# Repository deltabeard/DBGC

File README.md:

# DBGC: Deltabeard's Game Boy Cartridge
A reprogrammable Game Boy cartridge that utilises the Raspberry Pi RP2040.

## Supported Features
- Support for No MBC, MBC1 and MBC3 games (but only in single-speed mode).
- Real Time Clock (RTC) with battery backup.
- FRAM 32KiB for save support.
- NOR Flash 16MiB with support upto 8MiB ROM size.
- Can only play the one game programmed in at compile time.
- USB-C firmware upgrade support.

## Proposed Features

- Support multiple games on NOR Flash.
- USB-C flash storage explorer to store and retrieve save files and ROMs.
- USB-C networking support.

### Flash Storage
The flash storage will be partitioned to allow the user to either support large ROM sizes or increased number of ROMs stored. By setting the maximum ROM size to a smaller value, there will be more space to store other ROMs on the *Storage* partition. An example partition scheme is shown below.

| Partition | Size | Purpose |
|-----------|  --: |---------|
| Firmware | 256KiB | Stores firmware for the RP2040 |
| Storage | Remainder | Wear-levelling filesystem holding ROMs and save files |

### USB-C Networking

By utilising RP2040 and TinyUSB features, the USB-C port can act as a networking device, which when attached to a host, will allow the RP2040 to connect to the Internet. Future features will allow supported Game Boy games to make connections to the internet.

## Notes
BOM is optimised for purchase from JLCPCB with SMT assembly. The cost of producing a single cart of this revision is approximately £15. This version of the PCB has major errors that can be seen in the [errata.md](https://github.com/deltabeard/DBGC/blob/master/errata.md) document. **Do not manufacture PCB version 0.3 or below**; instead wait for the next version or the one on the master branch. 

# License

The majority of the software within this project are licensed under the 
terms of the ISC License. Please see the header of each source file for 
license terms. In brief, the copyright and permission notices must not be
modified.

The PCB schematic and layout are licensed under the 
Creative Commons Attribution-ShareAlike 4.0 International (CC BY-SA 4.0) 
license. In brief, you may modify and share but only under the same license 
to allow others to continue modifying and sharing.

This project includes
[Libbet and the Magic Floor](https://github.com/pinobatch/libbet) and
[2048-gb](https://github.com/Sanqui/2048-gb), which are both 
licensed under the terms of the zlib license, and are included within this
project in an unmodified binary form for testing purposes.

# Showcase

- [Pokemon Polished Crystal](https://github.com/Rangi42/polishedcrystal). A 
  major fan-made upgrade to Pokemon Crystal. Uses MBC3 with battery backed 
  SRAM and Real Time Clock. The version tested had CGB double-speed disabled,
  which caused minor graphical glitches within the game. An effort is made to
  fix these graphical glitches at https://github.com/deltabeard/polishedcrystal.
  DBGC does not currently support double-speed, so using it to play
  Polished Crystal may not result in the intended experience.

- Mega Man 1. This commercial game uses MBC1 ROM banking.

- [2048-gb](https://github.com/Sanqui/2048-gb). Open source homebrew game. 
  Uses no ROM banking.

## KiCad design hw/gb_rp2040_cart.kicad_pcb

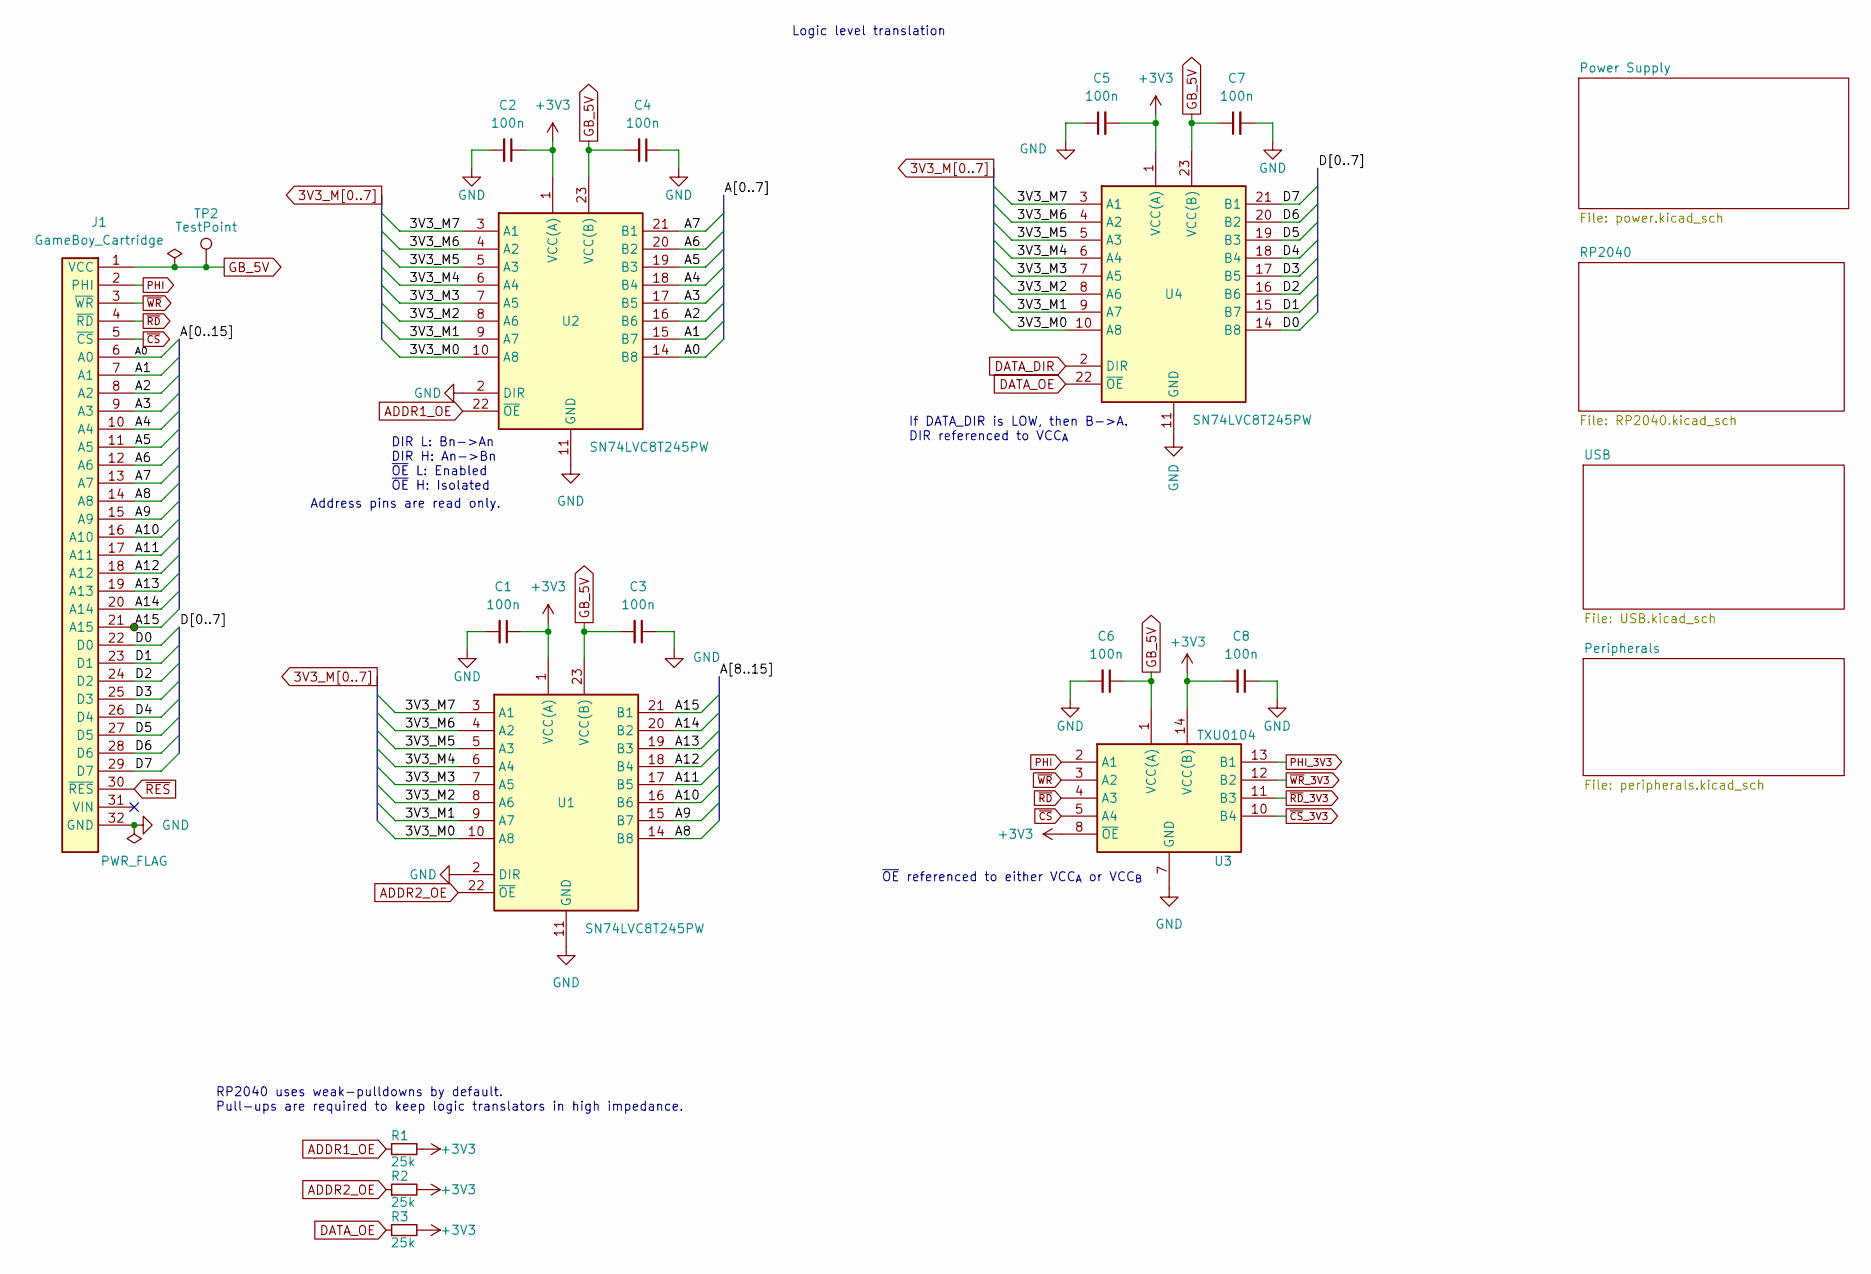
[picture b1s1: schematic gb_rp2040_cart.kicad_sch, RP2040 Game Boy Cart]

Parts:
C1, C2, C3, C4, C5, C6, C7, C8: 100n; C_0402_1005Metric; LCSC C1525
J1: GameBoy_Cartridge; GameBoy_Cartridge_1x32_P1.50mm_Full
R1, R2, R3: 25k; R_0402_1005Metric; LCSC C25900
TP1, TP2: TestPoint; TestPoint_Pad_D1.0mm
U1, U2, U4: SN74LVC8T245PW; TSSOP-24_4.4x7.8mm_P0.65mm; LCSC C27643
U3: TXU0104; TSSOP-14_4.4x5mm_P0.65mm

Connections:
3V3_M0: U1.10 (A8), U2.10 (A8), U4.10 (A8); also elsewhere on the board
3V3_M1: U1.9 (A7), U2.9 (A7), U4.9 (A7); also elsewhere on the board
3V3_M2: U1.8 (A6), U2.8 (A6), U4.8 (A6); also elsewhere on the board
3V3_M3: U1.7 (A5), U2.7 (A5), U4.7 (A5); also elsewhere on the board
3V3_M4: U1.6 (A4), U2.6 (A4), U4.6 (A4); also elsewhere on the board
3V3_M5: U1.5 (A3), U2.5 (A3), U4.5 (A3); also elsewhere on the board
3V3_M6: U1.4 (A2), U2.4 (A2), U4.4 (A2); also elsewhere on the board
3V3_M7: U1.3 (A1), U2.3 (A1), U4.3 (A1); also elsewhere on the board
/A0: J1.6 (A0), U2.14 (B8)
/A1: J1.7 (A1), U2.15 (B7)
/A2: J1.8 (A2), U2.16 (B6)
/A3: J1.9 (A3), U2.17 (B5)
/A4: J1.10 (A4), U2.18 (B4)
/A5: J1.11 (A5), U2.19 (B3)
/A6: J1.12 (A6), U2.20 (B2)
/A7: J1.13 (A7), U2.21 (B1)
/A8: J1.14 (A8), U1.14 (B8)
/A9: J1.15 (A9), U1.15 (B7)
/A10: J1.16 (A10), U1.16 (B6)
/A11: J1.17 (A11), U1.17 (B5)
/A12: J1.18 (A12), U1.18 (B4)
/A13: J1.19 (A13), U1.19 (B3)
/A14: J1.20 (A14), U1.20 (B2)
/A15: J1.21 (A15), TP1.1, U1.21 (B1)
/D0: J1.22 (D0), U4.14 (B8)
/D1: J1.23 (D1), U4.15 (B7)
/D2: J1.24 (D2), U4.16 (B6)
/D3: J1.25 (D3), U4.17 (B5)
/D4: J1.26 (D4), U4.18 (B4)
/D5: J1.27 (D5), U4.19 (B3)
/D6: J1.28 (D6), U4.20 (B2)
/D7: J1.29 (D7), U4.21 (B1)
DATA_DIR: U4.2 (DIR); also elsewhere on the board
DATA_OE: R3.1, U4.22 (~OE); also elsewhere on the board
GB_5V: C3.2, C4.2, C6.1, C7.1, J1.1 (VCC), TP2.1, U1.23 (VCC(B)), U1.24 (VCC(B)), U2.23 (VCC(B)), U2.24 (VCC(B)), U3.1 (VCC(A)), U4.23 (VCC(B)), U4.24 (VCC(B)); also elsewhere on the board
PHI: J1.2 (PHI), U3.2 (A1)
PHI_3V3: U3.13 (B1); also elsewhere on the board
~CS: J1.5 (~CS), U3.5 (A4)
~CS_3V3: U3.10 (B4); also elsewhere on the board
~RD: J1.4 (~RD), U3.4 (A3)
~RD_3V3: U3.11 (B3); also elsewhere on the board
~RES: J1.30 (~RES); also elsewhere on the board
~WR: J1.3 (~WR), U3.3 (A2)
~WR_3V3: U3.12 (B2); also elsewhere on the board

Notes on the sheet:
RP2040 uses weak-pulldowns by default. Pull-ups are required to keep logic translators in high impedance.
Address pins are read only.
DIR L: Bn->An DIR H: An->Bn ~{OE} L: Enabled ~{OE} H: Isolated
Logic level translation
~{OE} referenced to either VCC_{A} or VCC_{B}
If DATA_DIR is LOW, then B->A. DIR referenced to VCC_{A}

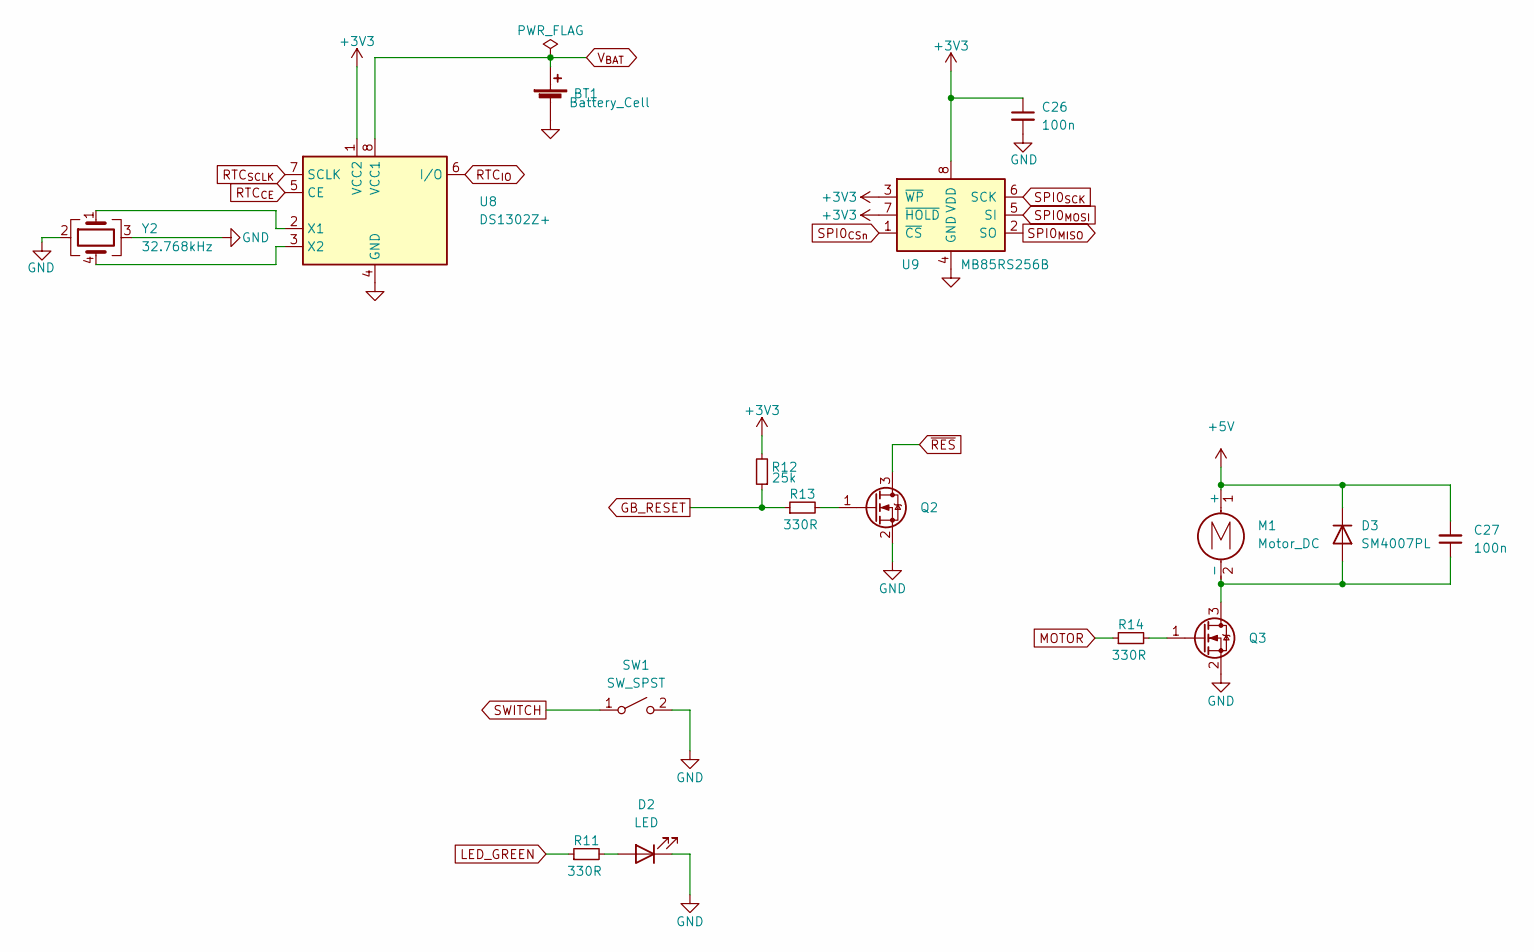
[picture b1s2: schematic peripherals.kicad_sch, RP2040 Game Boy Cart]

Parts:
BT1: Battery_Cell; MY-2032-11; LCSC C964835
C26, C27: 100n; C_0402_1005Metric; LCSC C1525
D2: LED; LED_0603_1608Metric; LCSC C2286
D3: SM4007PL; D_SOD-123F; LCSC C64898
M1: Motor_DC; PinHeader_1x02_P1.27mm_Vertical
Q2, Q3: N-Channel; SOT-23; LCSC C8545
R11, R13, R14: 330R; R_0603_1608Metric; LCSC C23138
R12: 25k; R_0402_1005Metric; LCSC C25900
SW1: SW_SPST; SW_SPST_TL3342; LCSC C318886
U8: DS1302Z+; SOIC-8_3.9x4.9mm_P1.27mm; LCSC C265479
U9: MB85RS256B; SOIC-8_3.9x4.9mm_P1.27mm; LCSC C8742
Y2: 32.768kHz; Crystal_SMD_Abracon_ABS25-4Pin_8.0x3.8mm; LCSC C252402

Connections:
+5V: C27.2, D3.1 (K), M1.1 (+); also elsewhere on the board
GB_RESET: R12.1, R13.1; also elsewhere on the board
LED_GREEN: R11.1; also elsewhere on the board
MOTOR: R14.1; also elsewhere on the board
unnamed: C27.1, D3.2 (A), M1.2 (-), Q3.3 (D)
unnamed: D2.2 (A), R11.2
unnamed: Q2.1 (G), R13.2
unnamed: Q3.1 (G), R14.2
unnamed: U8.2 (X1), Y2.1
unnamed: U8.3 (X2), Y2.4
RTC_{CE}: U8.5 (CE); also elsewhere on the board
RTC_{IO}: U8.6 (I/O); also elsewhere on the board
RTC_{SCLK}: U8.7 (SCLK); also elsewhere on the board
SPI0_{CSn}: U9.1 (~CS); also elsewhere on the board
SPI0_{MISO}: U9.2 (SO); also elsewhere on the board
SPI0_{MOSI}: U9.5 (SI); also elsewhere on the board
SPI0_{SCK}: U9.6 (SCK); also elsewhere on the board
SWITCH: SW1.1 (A); also elsewhere on the board
V_{BAT}: BT1.1 (+), U8.8 (VCC1)
~RES: Q2.3 (D); also elsewhere on the board

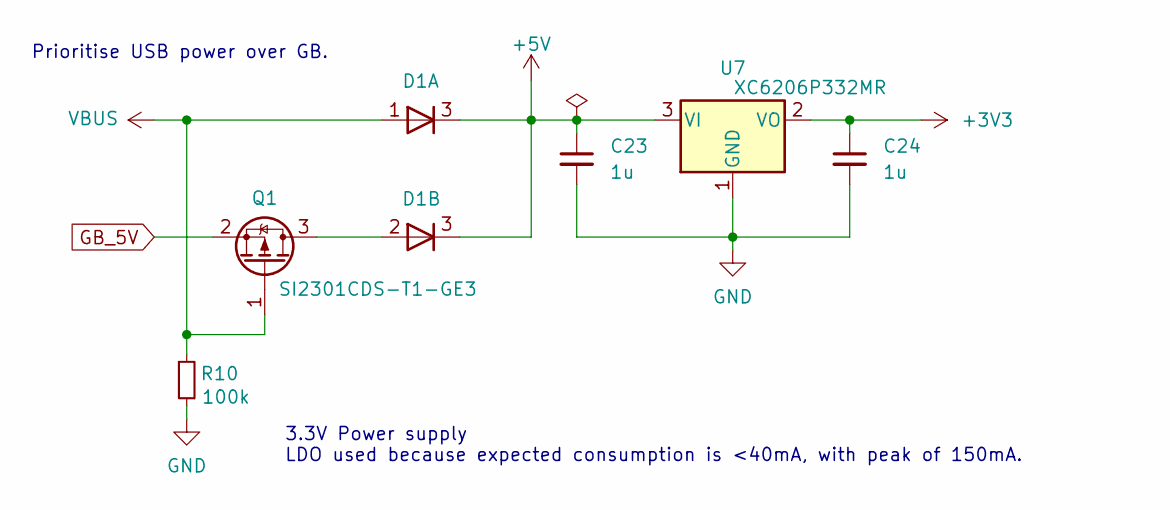
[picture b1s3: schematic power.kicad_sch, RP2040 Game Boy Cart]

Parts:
C23, C24: 1u; C_0402_1005Metric; LCSC C52923
D1: D_Dual_CommonCathode_AAK_Split; SOT-23; LCSC C68978
Q1: SI2301CDS-T1-GE3; SOT-23; LCSC C10487
R10: 100k; R_0603_1608Metric; LCSC C25803
U7: XC6206P332MR; SOT-23; LCSC C5446

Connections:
+5V: C23.1, D1.3 (K), U7.3 (VI); also elsewhere on the board
GB_5V: Q1.2 (S); also elsewhere on the board
unnamed: D1.2 (K), Q1.3 (D)
VBUS: D1.1 (A), Q1.1 (G), R10.1; also elsewhere on the board

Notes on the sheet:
Prioritise USB power over GB.
3.3V Power supply LDO used because expected consumption is <40mA, with peak of 150mA.

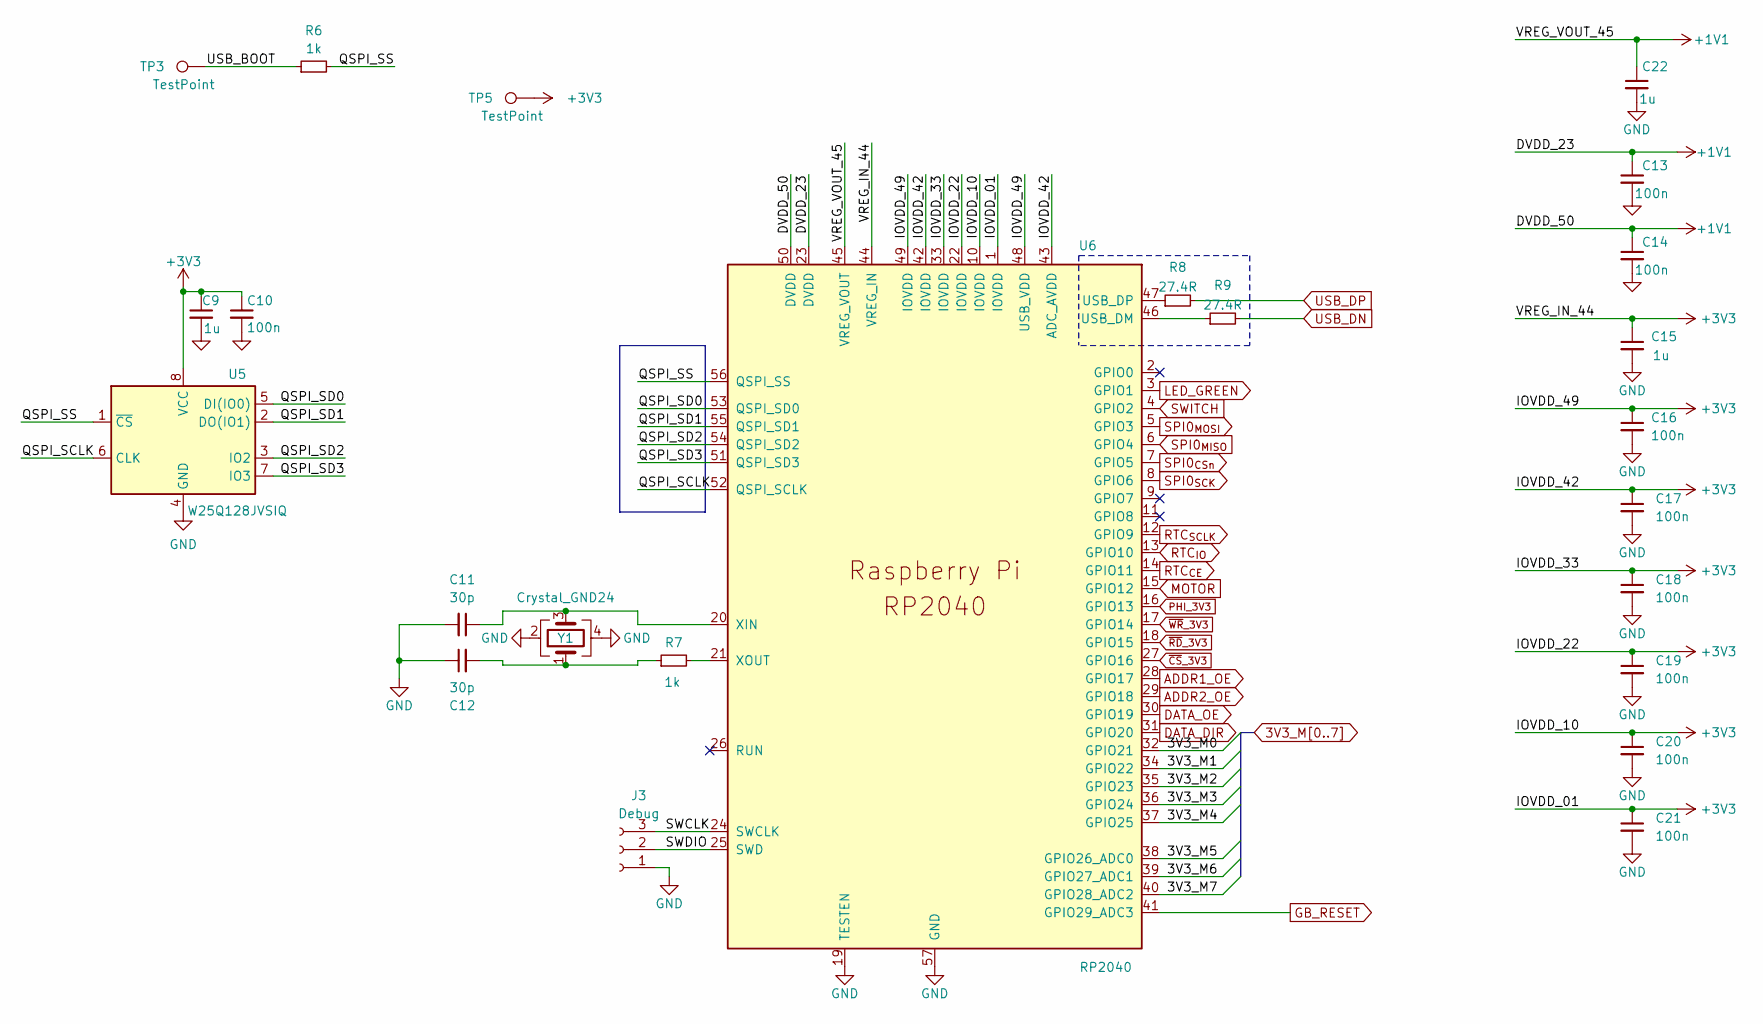
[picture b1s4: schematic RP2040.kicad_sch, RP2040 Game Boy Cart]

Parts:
C9, C15, C22: 1u; C_0402_1005Metric; LCSC C52923
C10, C13, C14, C16, C17, C18, C19, C20, C21: 100n; C_0402_1005Metric; LCSC C1525
C11, C12: 30p; C_0402_1005Metric; LCSC C1570
J3: Debug; PinSocket_1x03_P1.27mm_Vertical
R6, R7: 1k; R_0603_1608Metric; LCSC C21190
R8, R9: 27.4R; R_0603_1608Metric; LCSC C25190
TP3, TP5: TestPoint; TestPoint_THTPad_D1.0mm_Drill0.5mm
U5: W25Q128JVSIQ; SOIC-8_5.23x5.23mm_P1.27mm; LCSC C97521
U6: RP2040; RP2040-QFN-56; LCSC C2040
Y1: Crystal_GND24; Crystal_SMD_3225-4Pin_3.2x2.5mm; LCSC C9002

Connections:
3V3_M0: U6.32 (GPIO21); also elsewhere on the board
3V3_M1: U6.34 (GPIO22); also elsewhere on the board
3V3_M2: U6.35 (GPIO23); also elsewhere on the board
3V3_M3: U6.36 (GPIO24); also elsewhere on the board
3V3_M4: U6.37 (GPIO25); also elsewhere on the board
3V3_M5: U6.38 (GPIO26_ADC0); also elsewhere on the board
3V3_M6: U6.39 (GPIO27_ADC1); also elsewhere on the board
3V3_M7: U6.40 (GPIO28_ADC2); also elsewhere on the board
+1V1: C13.1, C14.1, C22.1, U6.23 (DVDD), U6.45 (VREG_VOUT), U6.50 (DVDD)
/RP2040/QSPI_SCLK: U5.6 (CLK), U6.52 (QSPI_SCLK)
/RP2040/QSPI_SD0: U5.5 (DI(IO0)), U6.53 (QSPI_SD0)
/RP2040/QSPI_SD1: U5.2 (DO(IO1)), U6.55 (QSPI_SD1)
/RP2040/QSPI_SD2: U5.3 (IO2), U6.54 (QSPI_SD2)
/RP2040/QSPI_SD3: U5.7 (IO3), U6.51 (QSPI_SD3)
/RP2040/QSPI_SS: R6.2, U5.1 (~CS), U6.56 (QSPI_SS)
/RP2040/SWCLK: J3.3, U6.24 (SWCLK)
/RP2040/SWDIO: J3.2, U6.25 (SWD)
/RP2040/USB_BOOT: R6.1, TP3.1
DATA_DIR: U6.31 (GPIO20); also elsewhere on the board
DATA_OE: U6.30 (GPIO19); also elsewhere on the board
GB_RESET: U6.41 (GPIO29_ADC3); also elsewhere on the board
LED_GREEN: U6.3 (GPIO1); also elsewhere on the board
MOTOR: U6.15 (GPIO12); also elsewhere on the board
unnamed: C11.1, U6.20 (XIN), Y1.3
unnamed: C12.2, R7.1, Y1.1
unnamed: R7.2, U6.21 (XOUT)
unnamed: R8.1, U6.47 (USB_DP)
unnamed: R9.1, U6.46 (USB_DM)
PHI_3V3: U6.16 (GPIO13); also elsewhere on the board
RTC_{CE}: U6.14 (GPIO11); also elsewhere on the board
RTC_{IO}: U6.13 (GPIO10); also elsewhere on the board
RTC_{SCLK}: U6.12 (GPIO9); also elsewhere on the board
SPI0_{CSn}: U6.7 (GPIO5); also elsewhere on the board
SPI0_{MISO}: U6.6 (GPIO4); also elsewhere on the board
SPI0_{MOSI}: U6.5 (GPIO3); also elsewhere on the board
SPI0_{SCK}: U6.8 (GPIO6); also elsewhere on the board
SWITCH: U6.4 (GPIO2); also elsewhere on the board
USB_DN: R9.2; also elsewhere on the board
USB_DP: R8.2; also elsewhere on the board
~CS_3V3: U6.27 (GPIO16); also elsewhere on the board
~RD_3V3: U6.18 (GPIO15); also elsewhere on the board
~WR_3V3: U6.17 (GPIO14); also elsewhere on the board

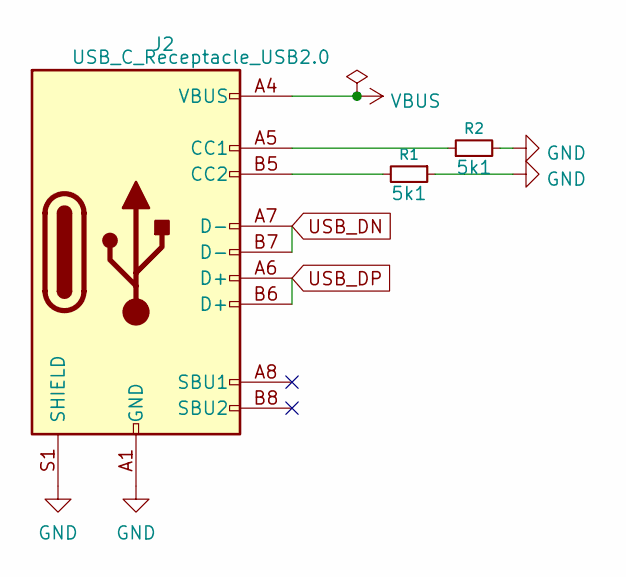
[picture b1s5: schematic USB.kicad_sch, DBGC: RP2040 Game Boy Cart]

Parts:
J2: USB_C_Receptacle_USB2.0; USB_C_Receptacle_Palconn_UTC16-G; LCSC C167321
R1, R2: 5k1; R_0603_1608Metric; LCSC C23186

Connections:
USB_DN: J2.A7 (D-), J2.B7 (D-); also elsewhere on the board
USB_DP: J2.A6 (D+), J2.B6 (D+); also elsewhere on the board
VBUS: J2.A4 (VBUS), J2.A9 (VBUS), J2.B4 (VBUS), J2.B9 (VBUS); also elsewhere on the board

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
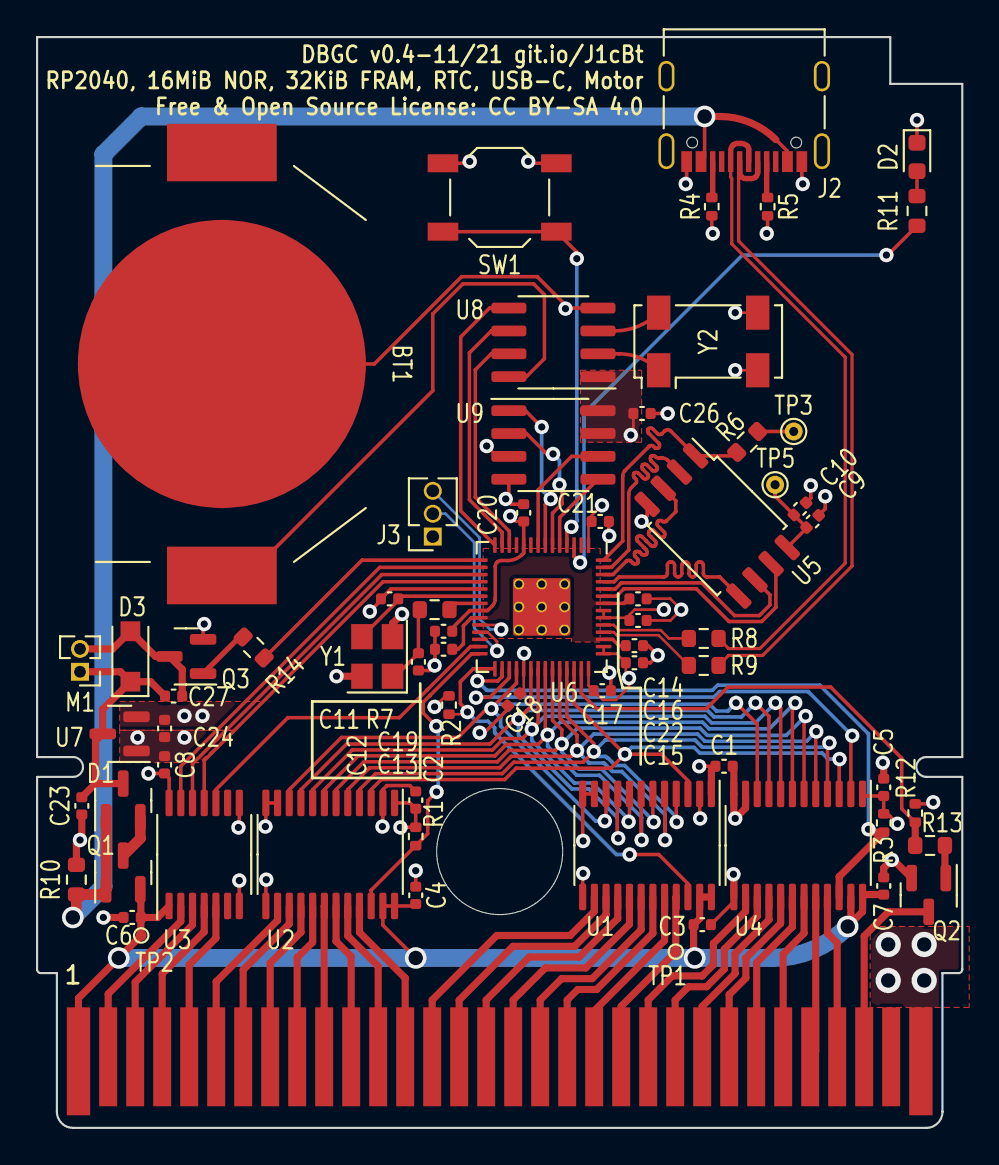
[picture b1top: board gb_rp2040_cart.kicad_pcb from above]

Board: 4 copper layers, 51.4 x 60.6 mm, 67 parts (0 on the bottom side), 88 nets.

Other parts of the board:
R4, R5: 5k1; R_0402_1005Metric

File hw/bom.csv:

Comment,Designator,Footprint,LCSC
"Battery_Cell","BT1","Project_Specific:MY-2032-11","C964835"
"100n","C1,C2,C3,C4,C5,C6,C7,C8,C10,C13,C14,C16,C17,C18,C19,C20,C21,C26,C27","Capacitor_SMD:C_0402_1005Metric","C1525"
"30p","C11,C12","Capacitor_SMD:C_0402_1005Metric","C1570"
"1u","C9,C15,C22,C23,C24","Capacitor_SMD:C_0402_1005Metric","C52923"
"D_Dual_CommonCathode_AAK_Split","D1","Package_TO_SOT_SMD:SOT-23","C68978"
"LED","D2","LED_SMD:LED_0603_1608Metric","C2286"
"SM4007PL","D3","Diode_SMD:D_SOD-123F","C64898"
"GameBoy_Cartridge","J1","Gekkio_Connector_PCBEdge:GameBoy_Cartridge_1x32_P1.50mm_Full",""
"USB_C_Receptacle_USB2.0","J2","Connector_USB:USB_C_Receptacle_Palconn_UTC16-G","C167321"
"Debug","J3","Connector_PinSocket_1.27mm:PinSocket_1x03_P1.27mm_Vertical",""
"Motor_DC","M1","Connector_PinHeader_1.27mm:PinHeader_1x02_P1.27mm_Vertical",""
"SI2301CDS-T1-GE3","Q1","Package_TO_SOT_SMD:SOT-23","C10487"
"N-Channel","Q2,Q3","Package_TO_SOT_SMD:SOT-23","C8545"
"25k","R1,R2,R3,R12","Resistor_SMD:R_0402_1005Metric","C25900"
"100k","R10","Resistor_SMD:R_0603_1608Metric","C25803"
"330R","R11,R13,R14","Resistor_SMD:R_0603_1608Metric","C23138"
"5k1","R4,R5","Resistor_SMD:R_0402_1005Metric","C25905"
"1k","R6,R7","Resistor_SMD:R_0603_1608Metric","C21190"
"27.4R","R8,R9","Resistor_SMD:R_0603_1608Metric","C25190"
"SW_SPST","SW1","Button_Switch_SMD:SW_SPST_TL3342","C318886"
"TestPoint","TP1,TP2","TestPoint:TestPoint_Pad_D1.0mm",""
"TestPoint","TP3,TP5","TestPoint:TestPoint_THTPad_D1.0mm_Drill0.5mm",""
"SN74LVC8T245PW","U1,U2,U4","Package_SO:TSSOP-24_4.4x7.8mm_P0.65mm","C27643"
"TXU0104","U3","Package_SO:TSSOP-14_4.4x5mm_P0.65mm",""
"W25Q128JVSIQ","U5","Package_SO:SOIC-8_5.23x5.23mm_P1.27mm","C97521"
"RP2040","U6","RP_RP2040:RP2040-QFN-56","C2040"
"XC6206P332MR","U7","Package_TO_SOT_SMD:SOT-23","C5446"
"DS1302Z+","U8","Package_SO:SOIC-8_3.9x4.9mm_P1.27mm","C265479"
"MB85RS256B","U9","Package_SO:SOIC-8_3.9x4.9mm_P1.27mm","C8742"
"Crystal_GND24","Y1","Crystal:Crystal_SMD_3225-4Pin_3.2x2.5mm","C9002"
"32.768kHz","Y2","Crystal:Crystal_SMD_Abracon_ABS25-4Pin_8.0x3.8mm","C252402"

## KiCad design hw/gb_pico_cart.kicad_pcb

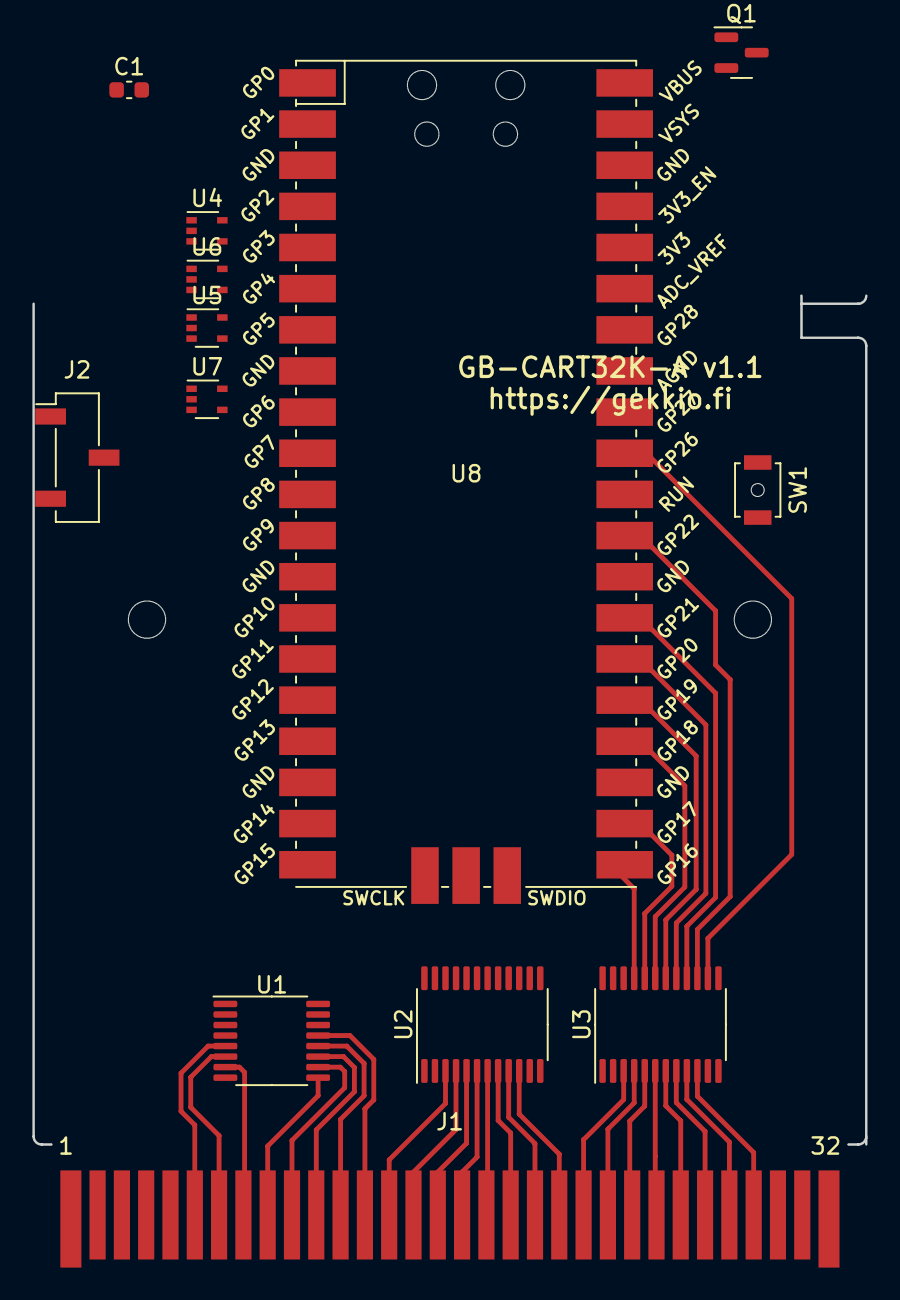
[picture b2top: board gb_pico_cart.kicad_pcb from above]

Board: 2 copper layers, 15 parts (0 on the bottom side), 59 nets.

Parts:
C1: 100n; C_0603_1608Metric
H2, H2#2: DNF; MountingHole_2.3mm
J1: GameBoy_Cartridge; GameBoy_Cartridge_1x32_P1.50mm_Edge
J2: DEBUG; PinSocket_1x03_P2.54mm_Vertical_SMD_Pin1Left
Q1: Si2319CDS; SOT-23
SW1: RESET; SW_SPST_B3U-1000P-B
U1: 74VHC9164FT; TSSOP-16_4.4x5mm_P0.65mm
U2, U3: 74LVC8T245PW; TSSOP-24_4.4x7.8mm_P0.65mm
U4, U5, U6, U7: SN74AUP1T34DCK; SOT-353_SC-70-5
U8: Pico; RPi_Pico_SMD_TH

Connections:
+3V3: C1.1, U1.1 (P/S_CONT), U1.16 (VCC), U2.23 (VCC(B)), U2.24 (VCC(B)), U3.23 (VCC(B)), U3.24 (VCC(B)), U4.5 (VCCB), U5.5 (VCCB), U6.5 (VCCB), U7.5 (VCCB), U8.36 (3V3)
+5V: J1.1 (VCC), Q1.3 (D), U2.1 (VCC(A)), U2.2 (DIR), U3.1 (VCC(A)), U4.1 (VCCA), U5.1 (VCCA), U6.1 (VCCA), U7.1 (VCCA)
/3V3_A8: U2.21 (B1), U8.11 (GPIO8)
/3V3_A9: U2.20 (B2), U8.12 (GPIO9)
/3V3_A10: U2.19 (B3), U8.14 (GPIO10)
/3V3_A11: U2.18 (B4), U8.15 (GPIO11)
/3V3_A12: U2.17 (B5), U8.16 (GPIO12)
/3V3_A13: U2.16 (B6), U8.17 (GPIO13)
/3V3_A14: U2.15 (B7), U8.19 (GPIO14)
/3V3_A15: U2.14 (B8), U8.20 (GPIO15)
/3V3_D0: U3.21 (B1), U8.21 (GPIO16)
/3V3_D1: U3.20 (B2), U8.22 (GPIO17)
/3V3_D2: U3.19 (B3), U8.24 (GPIO18)
/3V3_D3: U3.18 (B4), U8.25 (GPIO19)
/3V3_D4: U3.17 (B5), U8.26 (GPIO20)
/3V3_D5: U3.16 (B6), U8.27 (GPIO21)
/3V3_D6: U3.15 (B7), U8.29 (GPIO22)
/3V3_D7: U3.14 (B8), U8.31 (GPIO26_ADC0)
/A0: J1.6 (A0), U1.5 (Q/D1)
/A1: J1.7 (A1), U1.6 (Q/D2)
/A2: J1.8 (A2), U1.7 (Q/D3)
/A3: J1.9 (A3), U1.9 (Q/D4)
/A4: J1.10 (A4), U1.10 (Q/D5)
/A5: J1.11 (A5), U1.11 (Q/D6)
/A6: J1.12 (A6), U1.12 (Q/D7)
/A7: J1.13 (A7), U1.13 (Q/D8)
/A8: J1.14 (A8), U2.3 (A1)
/A9: J1.15 (A9), U2.4 (A2)
/A10: J1.16 (A10), U2.5 (A3)
/A11: J1.17 (A11), U2.6 (A4)
/A12: J1.18 (A12), U2.7 (A5)
/A13: J1.19 (A13), U2.8 (A6)
/A14: J1.20 (A14), U2.9 (A7)
/A15: J1.21 (A15), U2.10 (A8)
/D0: J1.22 (D0), U3.3 (A1)
/D1: J1.23 (D1), U3.4 (A2)
/D2: J1.24 (D2), U3.5 (A3)
/D3: J1.25 (D3), U3.6 (A4)
/D4: J1.26 (D4), U3.7 (A5)
/D5: J1.27 (D5), U3.8 (A6)
/D6: J1.28 (D6), U3.9 (A7)
/D7: J1.29 (D7), U3.10 (A8)
/SWCLK: J2.3, U8.41 (SWCLK)
/SWDIO: J2.1, U8.43 (SWDIO)
GND: C1.2, J1.32 (GND), J2.2, SW1.2, U1.3 (SI), U1.8 (GND), U2.11 (GND), U2.12 (GND), U2.13 (GND), U2.22 (~OE), U3.11 (GND), U3.12 (GND), U3.13 (GND), U3.22 (~OE), U4.3 (GND), U5.3 (GND), U6.3 (GND), U7.3 (GND), U8.3 (GND), U8.8 (GND), U8.13 (GND), U8.18 (GND), U8.23 (GND), U8.28 (GND), U8.33 (AGND), U8.38 (GND), U8.42 (GND)
LSB_ADDR_SERIAL: U1.14 (Q8'), U8.2 (GPIO1)
unnamed: Q1.1 (G), U8.40 (VBUS)
unnamed: Q1.2 (S), U8.39 (VSYS)
PHI: J1.2 (PHI), U4.2 (A)
PHI_3V3: U4.4 (B), U8.5 (GPIO3)
RUN: SW1.1, U8.30 (RUN)
SCK: U1.4 (CK), U8.4 (GPIO2)
~CS: J1.5 (~CS), U7.2 (A)
~CS_3V3: U7.4 (B), U8.9 (GPIO6)
~RD: J1.4 (~RD), U3.2 (DIR), U5.2 (A)
~RD_3V3: U5.4 (B), U8.7 (GPIO5)
~SEL_LOW_ADDR: U1.2 (~CLR_LOAD), U8.1 (GPIO0)
~WR: J1.3 (~WR), U6.2 (A)
~WR_3V3: U6.4 (B), U8.6 (GPIO4)

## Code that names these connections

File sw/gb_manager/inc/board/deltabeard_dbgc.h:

/*
 * Copyright (c) 2020 Raspberry Pi (Trading) Ltd.
 *
 * SPDX-License-Identifier: BSD-3-Clause
 */

// -----------------------------------------------------
// NOTE: THIS HEADER IS ALSO INCLUDED BY ASSEMBLER SO
//       SHOULD ONLY CONSIST OF PREPROCESSOR DIRECTIVES
// -----------------------------------------------------

#ifndef _BOARDS_DELTABEARD_DBGC_H
#define _BOARDS_DELTABEARD_DBGC_H

// For board detection
#define DELTABEARD_DBGC

// On some samples, the xosc can take longer to stabilize than is usual
#ifndef PICO_XOSC_STARTUP_DELAY_MULTIPLIER
#define PICO_XOSC_STARTUP_DELAY_MULTIPLIER 64
#endif

// --- GPIO ---
#define GPIO_LED_GREEN		1
#define GPIO_SWITCH		2
#define GPIO_MOTOR		12
#define GPIO_GB_RESET		29

// --- SPI0 ---
/* The READ command is not compatible with 33MHz operation. Use FSTRD
 * instead. */
#define MB85RS256B_BAUDRATE	(33 * 1000 * 1000)
#define SPI_MOSI		3
#define SPI_MISO		4
#define SPI_CSn			5
#define SPI_SCK			6

// --- PIO0 ---
#define GB_BUS_PIO		pio0
#define PIO_PHI			13
#define PIO_NWR			14
#define PIO_NRD			15
#define PIO_NCS			16
#define PIO_ADDR1_OE		17
#define PIO_ADDR2_OE		18
#define PIO_DATA_OE		19
#define PIO_DATA_DIR		20
#define PIO_M0			21
#define PIO_M7			28
#define NUM_MULTIPLEX_PINS	(PIO_M7 - PIO_M0) + 1
// PIO0: Static state machine configuration.
#define PIO_SM_A15		0
#define PIO_SM_NCS		1
#define PIO_SM_DO		2
#define PIO_SM_DI		3

// --- PIO1 ---
#define RTC_BUS_PIO		pio1
#define PIO_RTC_SCLK		9
#define PIO_RTC_IO		10
#define GPIO_RTC_CE		11
// PIO1: Static state machine configuration
#define PIO1_SM_RTC_WR		0
#define PIO1_SM_RTC_RD		1

// --- FLASH ---
#define PICO_BOOT_STAGE2_CHOOSE_W25Q080 1

#ifndef PICO_FLASH_SPI_CLKDIV
#define PICO_FLASH_SPI_CLKDIV 2
#endif

#ifndef PICO_FLASH_SIZE_BYTES
#define PICO_FLASH_SIZE_BYTES (16 * 1024 * 1024)
#endif

// All boards have B1 RP2040
#ifndef PICO_FLOAT_SUPPORT_ROM_V1
#define PICO_FLOAT_SUPPORT_ROM_V1 0
#endif

#ifndef PICO_DOUBLE_SUPPORT_ROM_V1
#define PICO_DOUBLE_SUPPORT_ROM_V1 0
#endif

#endif

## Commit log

2021-08-23 gb: add cursor & joypad ocntrol
2021-08-24 Finish schematic
2021-08-24 Refactor external footprints & libraries
2021-08-24 Add full DMG cart footprint
2021-08-24 Use RP2040 instead of Pico
2021-08-25 hw: connect cart to RP2040
2021-08-26 hw: start PCB layout
2021-08-28 hw: finish layout
2021-08-30 Finish routing & final checks
2021-08-31 Simplify circuit
2021-09-01 Layout components of simplified circuit
2021-09-02 Complete layout and start placing tracks
2021-09-04 sw: add cmake support
2021-09-04 all: fix root CMakeLists
2021-09-05 all: add descriptions to CMakeLists
2021-09-05 rp2040: begin writing bus PIO
2021-09-05 rp2040: simplify PIO for ro ROM
2021-09-05 rp2040: complete read-only PIO code
2021-09-06 rp2040: complete PIO program
2021-09-06 rp2040: add C code to PIO
2021-09-06 all: add PIO and fix CMake project call
2021-09-08 rp2040: allow data writing to cart in PIO
2021-09-08 hw: add fix for data direction
2021-09-08 hw: Add 0.1 errata
2021-09-08 rp2040: add PIO to CMakeLists & fix syntax errors
2021-09-09 hw: use parts from LCSC
2021-09-11 hw: complete 2-layer PCB
2021-09-11 hw: replace RTC
2021-09-13 hw: complete routing
    Use components available on LCSC.
2021-09-13 hw: add preview images
2021-09-13 README: Create file
2021-09-13 hw: add more information to BOM
2021-09-16 README: add feature list
2021-09-22 hw: add RTC & IO Expander support
2021-09-22 hw: fix conversion of GB Manager on build
2021-09-23 hw: add IRQ for GB read data state machine
2021-09-24 hw: add USB HID support
2021-09-25 sw: fix compiling on Linux
2021-09-28 hw: fix USB
    Additionally reduced the size of the battery holder.
2021-09-28 sw: add usb serial
2021-09-28 sw: add verification tool
2021-09-28 sw: verify: add terminal
2021-09-29 hw: add BOOTSEL button and routing changes
2021-09-29 sw: verify: add I2C commands
2021-09-30 README: update flash storage partition map
2021-09-30 hw: use CR2032 footprint & larger testpoints
2021-09-30 sw: add RTC date and temperature commands
2021-10-01 sw: verify: add backspace support
2021-10-01 sw: verify: fix PIO read & add BUS viewer
2021-10-02 sw: add basic implementation for testing GB Bus
2021-10-02 sw: verify: displays logo correctly
2021-10-03 sw: verify: remove unused file
2021-10-03 sw: verify: fix data direction logic
2021-10-04 sw: verify: use IRQ for waiting in PIO
2021-10-04 sw: verify: use dual I/O boot_stage2
    Additionally renamed the PIO programs to be more descriptive of their
    functions.
2021-10-04 sw: verify: minor cleanup
2021-10-05 sw: basic: further simplify
2021-10-06 sw: perform clock speed tests
2021-10-06 sw: Minor changes to freq
2021-10-06 hw: use nets for decoupling capacitors
2021-10-06 sw: verify: get past boot screen
2021-10-07 sw: verify: write to specific byte in PIO FIFO
2021-10-07 Revert "sw: verify: write to specific byte in PIO FIFO"
    This reverts commit 3958661f8cf03c718db780ac8a97372e60276e9e.
2021-10-07 sw: verify: optimise PIO a bit
2021-10-07 sw: verify: remove overclocking in PIO function
2021-10-08 More attempts
2021-10-09 sw: verify: move PIO to core1
2021-10-10 sw: verify: working example
2021-10-11 sw: fix building GB manager
    Additionally added a custom panic function to reboot to reprogramming
    mode on fatal error.
2021-10-13 sw: verify: overclock flash for required speed
2021-10-13 sw: verify: remove unneeded delay in PIO
2021-10-13 sw: verify: attempt to add MBC1 support
2021-10-14 sw: verify: working MBC1
    Fixed an issue whereby flash reads were taking longer than required.
2021-10-14 sw: remove boot_stage2 test
2021-10-14 hw: minor rearranging of symbols
2021-10-16 sw: verify: add MBC1 RAM support
2021-10-17 sw: gb: add emulator for DBGC Cart API
    Peanut-GB is repurposed to emulate the DBGC Cart API. This API is used
    to obtain the ROM list from the DBGC cart and to allow the user to
    select their game.
2021-10-17 sw: gb: remove ram functions
2021-10-17 sw: add MBC3 and bus traceback
2021-10-19 sw: WIP to improve flash read speed
2021-10-20 sw: basic: remove USB support
    Instead, use double reset to USBBOOT.
    Also, strip libbet.gb to use less space.
2021-10-20 sw: basic: minor change to order of PIO command
    Prepare the X register before waiting for low edge of PHI clock.
2021-10-20 sw: basic: fix GB power setting
2021-10-21 sw: refactor source
2021-10-21 sw: make emulator use the command line on MSVC
2021-10-21 sw: emulate cart turning off
2021-10-21 sw: fix rom listing
2021-10-22 sw: change cart API address to logo
    This stops the use of the interrupt locations in ROM.
2021-10-22 sw: remove delay on write signal
2021-10-22 sw: remove MBC2 support & fix unused RAM size
2021-10-24 hw: multiplex Game Boy bus pins
2021-10-25 hw: begin layout
2021-10-27 Revert "sw: remove delay on write signal"
    This reverts commit 3fb5d1da0ae374292fb2c3d9dcd2a045d4bf861d.
2021-10-28 sw: fix ROM banking
2021-10-28 hw: WIP
2021-10-28 sw: comment on data ready delay to 1 cycle
2021-10-30 sw: simplify verify & add FRAM save
    Saving with FRAM causes a fault in the GB Bus communication.
2021-10-30 meta: create errata.md document
2021-10-30 README: add features & showcase
2021-10-30 README: add cost information
2021-10-30 README: minor fixes
2021-10-30 all: Add open source license
2021-10-31 README: remove ambiguous license statement
2021-10-31 sw: fix saving to FRAM
    Saving to FRAM is done by pressing the button.
2021-11-01 sw: add comments throughout
2021-11-01 sw: fix mgmt code block not removed
2021-11-01 sw: cache Bank0 in XIP cache-as-SRAM
2021-11-01 sw: push button on power-on to USBBOOT
2021-11-07 sw: verify: simplify FRAM dumping
2021-11-07 sw: manager: allow for 4MiB MBC3 ROMs
2021-11-09 manager: use atomics & reduce clock speed
2021-11-11 sw: force i2c function into RAM
2021-11-11 sw: read data from gb manager at BANK0 addresses
2021-11-11 sw: remove atomics todo
2021-11-11 sw: increase core clock slightly
    I had one crash after two hours of gameplay, which could be due to a
    missed clock cycle.
2021-11-11 sw: use events for low power second core
    Instead of using a busy loop on the second core, sleep and wait for an
    event after a timeout is calculated on the first core.
2021-11-11 sw: remove header file from sources list
2021-11-11 sw: use RAM function for I2C writes
2021-11-13 Revert "sw: use RAM function for I2C writes"
    This reverts commit a6971874b09dea2a477451fc3da306e201b12757.
2021-11-13 Revert "sw: force i2c function into RAM"
    This reverts commit 4ecf91308a94141c7efec92500e1069299468e2b.
2021-11-14 hw: remove DIP switch and LED
2021-11-14 sw: add RTC & use low power sleep
2021-11-16 hw: route multiplexed gb bus circuit
    The lower address, higher address and data bits are multiplexed together
    to a single 8-bit bus on the RP2040. This allows the FRAM to be
    connected via SPI for faster communication speed, and allows for a
    cheaper RTC component to be used. Furthermore, a vibration motor has
    been added.
2021-11-17 README: update features
2021-11-17 sw: add hello-world program for DMG
2021-11-18 sw: add halt to hello world
2021-11-18 sw: dmg: reduce tiles bitmap
2021-11-18 sw: dmg: use interrupts for vblank delay
2021-11-19 sw: dmg: fix memcpy routine
2021-11-23 sw: dmg: use qword memcpy & use macros
    Improved the readability of the code by making use of macros and
    preprocessor.
2021-11-23 sw: dmg: remove unused labels
2021-11-24 sw: dmg: print hello world in custom font
    Font is public domain by Reddit user graspee.
2021-11-24 sw: dmg: fix bitness of font in makefile
2021-11-26 sw: dmg: improve charset definition
2021-11-26 sw: dmg: optimisations & use window for menu name
2021-11-26 sw: dmg: center align menu title
2021-11-27 sw: dmg: optimisations
2021-11-28 dmg: attempt to add cursor
2021-11-28 dmg: fix OAM glitches & workaround DMG IRQ errata
2021-11-28 dmg: limit scroll speed
2021-11-28 dmg: minor improvements to input
2021-12-02 sw: significant work for v0.4
    Started work on DS1302 PIO communication.
    LED is tested working.
2021-12-03 sw: verify: reduce power consumption
2021-12-03 sw: verify: add IRQ atomics to DS1302 PIO
2021-12-03 sw: verify: add INFO command
2021-12-03 sw: verify: minor changes to ds1302 PIO
2021-12-04 sw: dmg: disable VBlank function until OAM init
2021-12-04 sw: dmg: fix moving cursor
2021-12-04 sw: dmg: move input checking to main routine
2021-12-04 sw: dmg: move cursor one tile at a time
2021-12-05 sw: verify: add DS1302 communication
2021-12-05 sw: dmg: only update screen on input change
2021-12-05 sw: dmg: move cursor on button press
2021-12-05 sw: dmg: minor optimisation in task management
2021-12-05 sw: dmg: limit cursor to number of entries
2021-12-06 sw: dmg: separate menu functions
2021-12-06 sw: dmg: fix menu entry size offset
2021-12-06 sw: dmg: WIP: working on dynamic menu loading
2021-12-07 sw: dmg: minor optimisation
2021-12-07 sw: dmg: WIP print entry name
2021-12-07 sw: dmg: dynamically handle menu entries
2021-12-08 sw: rewrite PIO for multiplexed GB Bus
2021-12-09 sw: add sm code
2021-12-10 sw: fix not setting IRQ on address read
2021-12-12 sw: working basic GB communication
2021-12-18 sw: fix GB comms with new PIO program
2021-12-24 sw: use interrupts for A15 handling
2021-12-26 sw: booting MBC1 test ROM (fails though)
2021-12-26 sw: fix MBC[1,3] ROM reads
2021-12-27 sw: fix saving to FRAM
2021-12-27 sw: only save to FRAM on cart write
    Additionally made the LED act as a FRAM writing indicator.
2021-12-27 sw: reduced overclocking

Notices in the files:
hw/RP2040.kicad_sch:
All Rights Reserved
hw/USB.kicad_sch:
Copyright (c) 2021 Mahyar Koshkouei
hw/gb_rp2040_cart.kicad_pcb:
Copyright © 2021 Mahyar Koshkouei, License: CC BY-SA 4.0.
Free & Open Source License: CC BY-SA 4.0
